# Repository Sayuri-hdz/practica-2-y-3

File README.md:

# Practice 2. Developiong the PCB (Layout)

## Objectives

Develop the connection diagrams (layout) from the schematic diagram.

## Introduction

Microcontrollers are all around  he world. Each day, Microcontrollers, are more present in the many aspects of our lives: in our work, inside our houses, and in more. We can find them controlling small devices like cellphones, microwaves, washing machines, and televisions.

A microcontroller is one device or chip that is used to govern one or more processes. For example, the controller that regulates the room temperature of an air conditioner; it has a sensor that continuously measures the internal temperature and, when the preset limits are exceeded, it generates the necessary signals to adjust the temperature.

## State of the Art

### The practices and the PIC microcontroller

The main objective of this practices is to provide students the foundation to fully understand the operation of the PIC18F45K50 microcontroller. This will be achieved through 11 documents that will guide the reader to create their own electronic card or Printed Circuit Board (PCB) and to be able to program it; in order to, execute different functions.

The advantages of ta PIC microcontroller to others on the market, which is why it will be used throughout this manual, are as follows:

- Easy to operate.
- There is enough documentation to work with it and it’s easy to obtain it.
- The price is comparatively lower than its competitors.
- It has a high operating speed.
- Development tools are cheap and easy to use.
- There are a variety of hardware that can record, erase and check the behavior of PIC.
- Once you learn to handle a PIC, it will easier to handle any other models of microcontrollers.

### KiCad EDA Software

KiCad is an open source software suite for Electronic Design Automation (EDA). The programs handle Schematic Capture,
and PCB Layout with Gerber output. The suite runs on Windows, Linux and macOS and is licensed under GNU GPL v3. The
first release date was in 1992 by its original author, Jean-Pierre Charras, but is now currently under development by
the KiCad Developers Team. 

## Results

In this section, you must report the outcomes of the laboratory activities.

### Follow the next 'Project Configuration' Steps

1. In  the  same  project  from  practice  1,  click  on  the  icon ‘Assign PCB footprints to schematic symbols’.  By  doing  so,  you  will  be  able  to  watch  the  footprints associations in a list format. ***NOTE:*** *If a ***‘Confirmation’*** window pops to reassign all the components to a new library format, click ‘No.’*

2. Now it is time to add the corresponding libraries to the Cvpcbprogram.   Download from [here](./modules)  the modules   needed   for   the   project.   Click   on Preferences→Manage Footprint Libraries...and  in this  way  you  will  be  able  to  add  the  modules  from the folder  named  ‘modules.’  Click  on  ‘Project  Specific Libraries...’  tab,  then  click  on  the  button  ‘Browse Libraries...’ and search for the folder  where  you  save the modules. Select all the files and click ‘OK.’Fig.  1 shows the result of the added modules. NOTE:Your KiCad EDA Software must be in english to add the modules.

3. Once  that  is  done,  you  must  associate  the  list  of components  with  its  respective  footprint using Table  I for  guidance.  Be  sure  to  activate  the  option  ‘Filter footprints  list  by  library’ from  the Cvpcbtoolbar. To associate  the  components  showed  in  the middle  column,  double  click  with  their  corresponding footprint from the right column. ***NOTE:*** *Search  all  the  footprints  in  the*  ***‘user’*** *and * 
***‘discrete’*** * added libraries that should be found at the end of the list.*

4. Save   your modifications  by  clicking  **‘Apply,  Save Schematic & Continue,’ and then click ‘OK.’**
5. After that, you may close the Cvpcband go back to the EESchema (Schematic  Editor.)  Save  your  project  by clicking   on File→Save.   Close   the   editor   of   the Schematic and switch back to the **‘Project Manager.’**

6. Once you have the design of the circuit on the schematic, it is time to generate the **‘layout’** of our PCB  using the Netlist  file. On  the Project  Manager program  from KiCad, click on the icon **‘PCB layout editor’** . A new window will appear from the PCBNew. Click **‘Yes’** in the confirmation window.
7. On  the  toolbar  menu  from  the PCBNew click  on  the **‘Page  Settings  for  paper  size  and  texts’**
and modify the size settings to **‘USLetter 8.5x11in.’**

8. After  that,  it  will be  time  to  focus  more  on  design concepts.  You  may  do  so  by  opening  the
menu  of **‘Setup→Design Rules...’**. On   it,   some   final   design characteristics will appear with many millimeter values. Between   them,   you   should   find  the  **‘Clearance’** specification  which  is  the  smallest  spaces  that  it  must exist  between  the tracks  on the  PCB.  You  shall  set the value of this cell to 0.508 mm (0.020 inches.) Next, we set  a  value  of 1.200  mm  (0.047244 inches)on the  cell of **‘Track Width.’** 

9. Switch now to the ‘Global Design Rules’ tab and write, if needed, the minimum values for each an every one of the parameters on the ‘Minimum Allowed Values’ box. Click ‘OK.’

10. Time  to  import  the  Netlist  file.  Go  to  the  toolbar ‘Tools→Update  PCB  from  Schematic...’  and  then click on ‘Update  PCB.’ When  you  close  the  window all the components will appear on the screen.

11.Check in the ‘Layers Manager’ window (located at the right  part  of  your  screen) that all  the needed  boxes  are
checked, as shown:

11.Check in the ‘Layers Manager’ window (located at the right  part  of  your  screen) that all  the needed  boxes  are checke

12. Now you  have  to  define  the  limits  of  the  PCB.  First, highlight  the  ‘Edge.Cuts’  layer.  Then,  select  the  ‘Add  graphic lines’ tool and began to trace the original measures of your copper board (15x20 cm.) You must also define the  cutting  area;  do  not  forget  to  add  a  2.5  cm  margin around the board. To measure the lines, you can use the ‘Add dimension’ tool located on the right.

13. It is your turn to move all the components in the circuit in  order  to  avoid  any  track  intersection  inside  the working   area.   You   can   move   the   components   by positioning your mouse pointer above it and pressing the key [G]. All the components are connected to each other by a group of wires called ratsnest. Make sure that the icon  of  **‘Hide  board  ratsnest’** located  in  the toolbar of the left is highlighted.

14. Now you must link all the connections of you PCB. But before  that,  you  must  change  the  drawing  option  from the right toolbar from ‘Edge.Cuts’ to ‘B.Cu (PgDn)’ (B->Bottom, Cu->Copper.).

15. Start to connect your tracks to each and every one pin on the schematic by using the icon ‘Route Tracks’. Trace  all  the  routes  for  each  net  or  connection  in  your PCB design.

16. Once  your  are  done,  save  your  layout  File->Save  or using the command [Ctrl + S].

17. Your board must look like:

### Report
For this practice, modify only the Conclusion section. Commit an push the changes on the fork of this repository and add
upload the link on Canvas.

### File uploads
Commit and push the files with extensions .pro and .kicad_pcb created once you completed all the steps of the document in the repository.

### Demonstration
Screenshot the image of the complete schematic and upload it at the repository.

## Conclusion

La  practica 2  me gustó porque nos envolvimos mucho en el diseño de tarjetas, la unica parte que me disgustó fue de acomodar todo en su lugar.
La parte que siento que me servira más es la parte donde elegí los componente para poderlos en la tarjeta, me sirvió para poder indentificar como son los simpolos de los componentes y el 3d viwer para ver  como son en la vida real los componentes. Fue de gran utilidad ya que en un futuro este tipo de programa lo podremos utilizar para  un futuro. La practica 3 fue muy sencilla, nos explican como verificar que lo que se hizo con las conexiones este bien y cambiamos unas configuraciones del programa.
Algo en lo que sigo teniendo conflicto es en subir todo a github, me revuelvo en las instrucciones y en todo lo que hay que subir. Desde mi punto de vista creo que esto es lo más dificil de todo.

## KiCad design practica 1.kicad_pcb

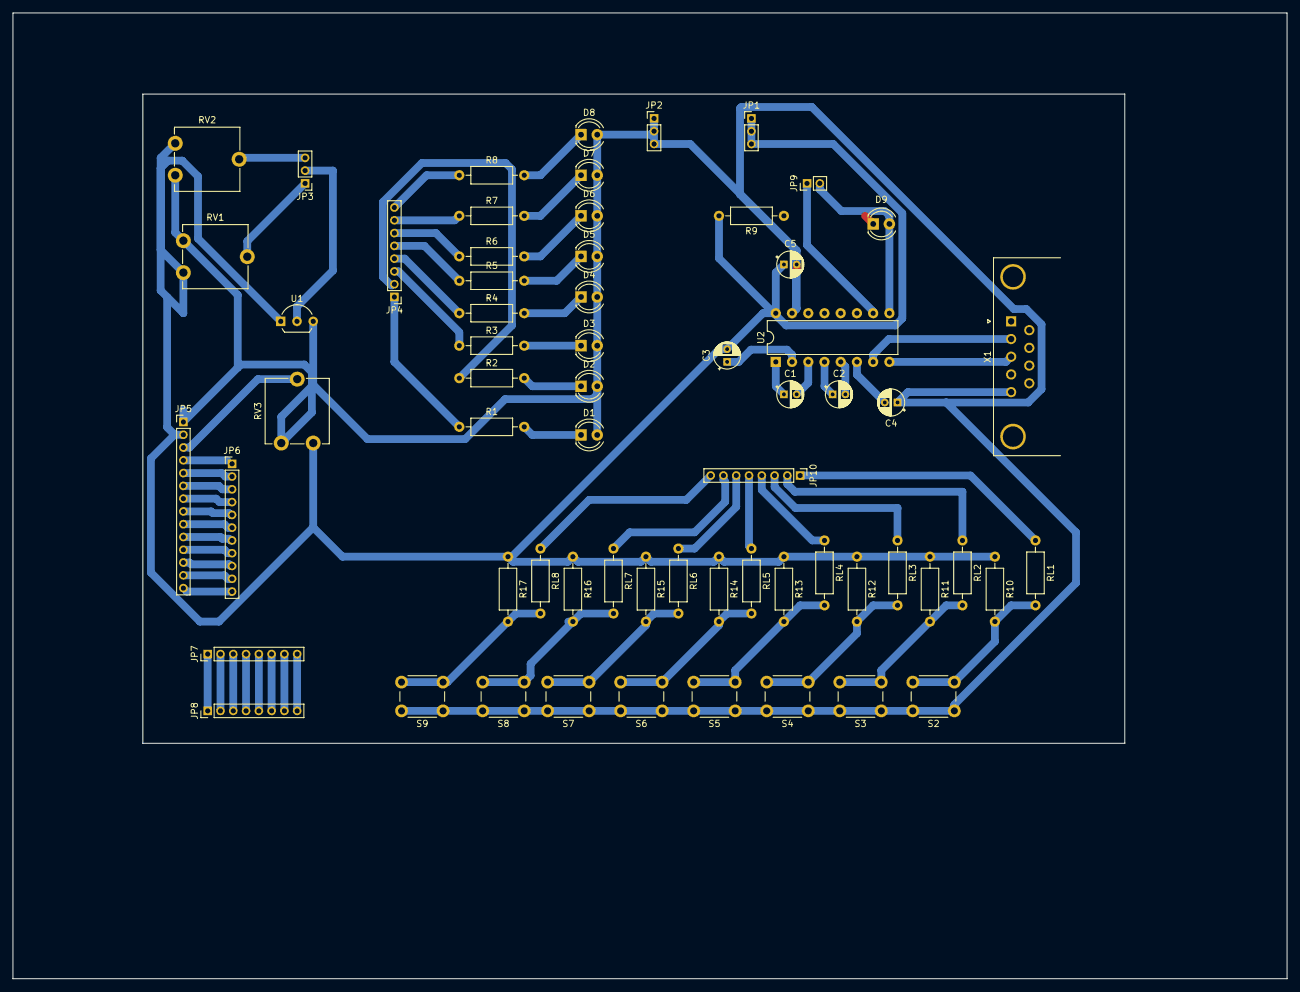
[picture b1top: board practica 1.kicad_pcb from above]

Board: 2 copper layers, 199.4 x 151.1 mm, 63 parts (0 on the bottom side), 68 nets.

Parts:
C1, C2, C3, C4, C5: 10u; CP_Radial_D4.0mm_P2.00mm
D1, D2, D3, D4, D5, D6, D7, D8, D9: LED; LED_D4.0mm
JP1, JP2, JP3: PINHD-1X3; PinHeader_1x03_P2.00mm_Vertical
JP4, JP7, JP8, JP10: PINHD-1X8; PinHeader_1x08_P2.00mm_Vertical
JP5: PINHD-1X14; PinHeader_1x14_P2.00mm_Vertical
JP6: PINHD-1X11; PinHeader_1x11_P2.00mm_Vertical
JP9: PINHD-1X2; PinHeader_1x02_P2.00mm_Vertical
R1, R2, R3, R4, R5, R6, R7, R8, R9: 470; R_Axial_DIN0207_L6.3mm_D2.5mm_P10.16mm_Horizontal
R10, R11, R12, R13, R14, R15, R16, R17: 4.7k; R_Axial_DIN0207_L6.3mm_D2.5mm_P10.16mm_Horizontal
RL1, RL2, RL3, RL4, RL5, RL6, RL7, RL8: 1K; R_Axial_DIN0207_L6.3mm_D2.5mm_P10.16mm_Horizontal
RV1, RV2: 10K; Potentiometer_ACP_CA9-V10_Vertical
RV3: POT; Potentiometer_ACP_CA9-V10_Vertical
S2, S3, S4, S5, S6, S7, S8, S9: SW_PUSH; SW_PUSH_6mm
U1: MCP9700A; TO-92L_Inline_Wide
U2: MAX232; DIP-16_W7.62mm
X1: F09HP; DSUB-9_Female_Horizontal_P2.77x2.84mm_EdgePinOffset4.94mm_H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

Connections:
+5VA: C3.2, C5.1, JP1.1, JP1.2, JP1.3, JP5.2, R9.2, R10.1, R11.1, R12.1, R13.1, R14.1, R15.1, R16.1, R17.1, RV1.1, RV2.3, RV3.1, U1.1, U2.16
GNDA: C4.1, C5.2, D1.2, D2.2, D3.2, D4.2, D5.2, D6.2, D7.2, D8.2, JP2.1, JP2.2, JP2.3, JP5.1, RV1.3, RV2.1, RV3.3, S2.1, S3.1, S4.1, S5.1, S6.1, S7.1, S8.1, S9.1, U1.3, U2.15, X1.5
unnamed: C1.1, U2.1
unnamed: C1.2, U2.3
unnamed: C2.1, U2.4
unnamed: C2.2, U2.5
unnamed: C3.1, U2.2
unnamed: C4.2, U2.6
unnamed: D1.1, R1.2
unnamed: D2.1, R2.2
unnamed: D3.1, R3.2
unnamed: D4.1, R4.2
unnamed: D5.1, R5.2
unnamed: D6.1, R6.2
unnamed: D7.1, R7.2
unnamed: D8.1, R8.2
unnamed: D9.1, R9.1
unnamed: D9.2, JP9.2, U2.9
unnamed: JP3.1, RV1.2
unnamed: JP3.2, U1.2
unnamed: JP3.3, RV2.2
unnamed: JP4.1, R1.1
unnamed: JP4.2, R2.1
unnamed: JP4.3, R3.1
unnamed: JP4.4, R4.1
unnamed: JP4.5, R5.1
unnamed: JP4.6, R6.1
unnamed: JP4.7, R7.1
unnamed: JP4.8, R8.1
unnamed: JP5.3, RV3.2
unnamed: JP5.4, JP6.1
unnamed: JP5.5, JP6.2
unnamed: JP5.6, JP6.3
unnamed: JP5.7, JP6.4
unnamed: JP5.8, JP6.5
unnamed: JP5.9, JP6.6
unnamed: JP5.10, JP6.7
unnamed: JP5.11, JP6.8
unnamed: JP5.12, JP6.9
unnamed: JP5.13, JP6.10
unnamed: JP5.14, JP6.11
unnamed: JP7.1, JP8.1
unnamed: JP7.2, JP8.2
unnamed: JP7.3, JP8.3
unnamed: JP7.4, JP8.4
unnamed: JP7.5, JP8.5
unnamed: JP7.6, JP8.6
unnamed: JP7.7, JP8.7
unnamed: JP7.8, JP8.8
unnamed: JP9.1, U2.10
unnamed: JP10.1, RL1.1
unnamed: JP10.2, RL2.1
unnamed: JP10.3, RL3.1
unnamed: JP10.4, RL4.1
unnamed: JP10.5, RL5.1
unnamed: JP10.6, RL6.1
unnamed: JP10.7, RL7.1
unnamed: JP10.8, RL8.1
unnamed: R10.2, RL1.2, S2.2
unnamed: R11.2, RL2.2, S3.2
unnamed: R12.2, RL3.2, S4.2
unnamed: R13.2, RL4.2, S5.2
unnamed: R14.2, RL5.2, S6.2
unnamed: R15.2, RL6.2, S7.2
unnamed: R16.2, RL7.2, S8.2
unnamed: R17.2, RL8.2, S9.2
unnamed: U2.7, X1.2
unnamed: U2.8, X1.3

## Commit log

2020-09-22 Update README.md for delivery
2020-09-22 Add files via upload
    profe, la practica 1 es la 2 y 3 solo que no le cambie el nombre porque estaba insegura de que iba a pasar si se lo cambiaba y asi lo deje
